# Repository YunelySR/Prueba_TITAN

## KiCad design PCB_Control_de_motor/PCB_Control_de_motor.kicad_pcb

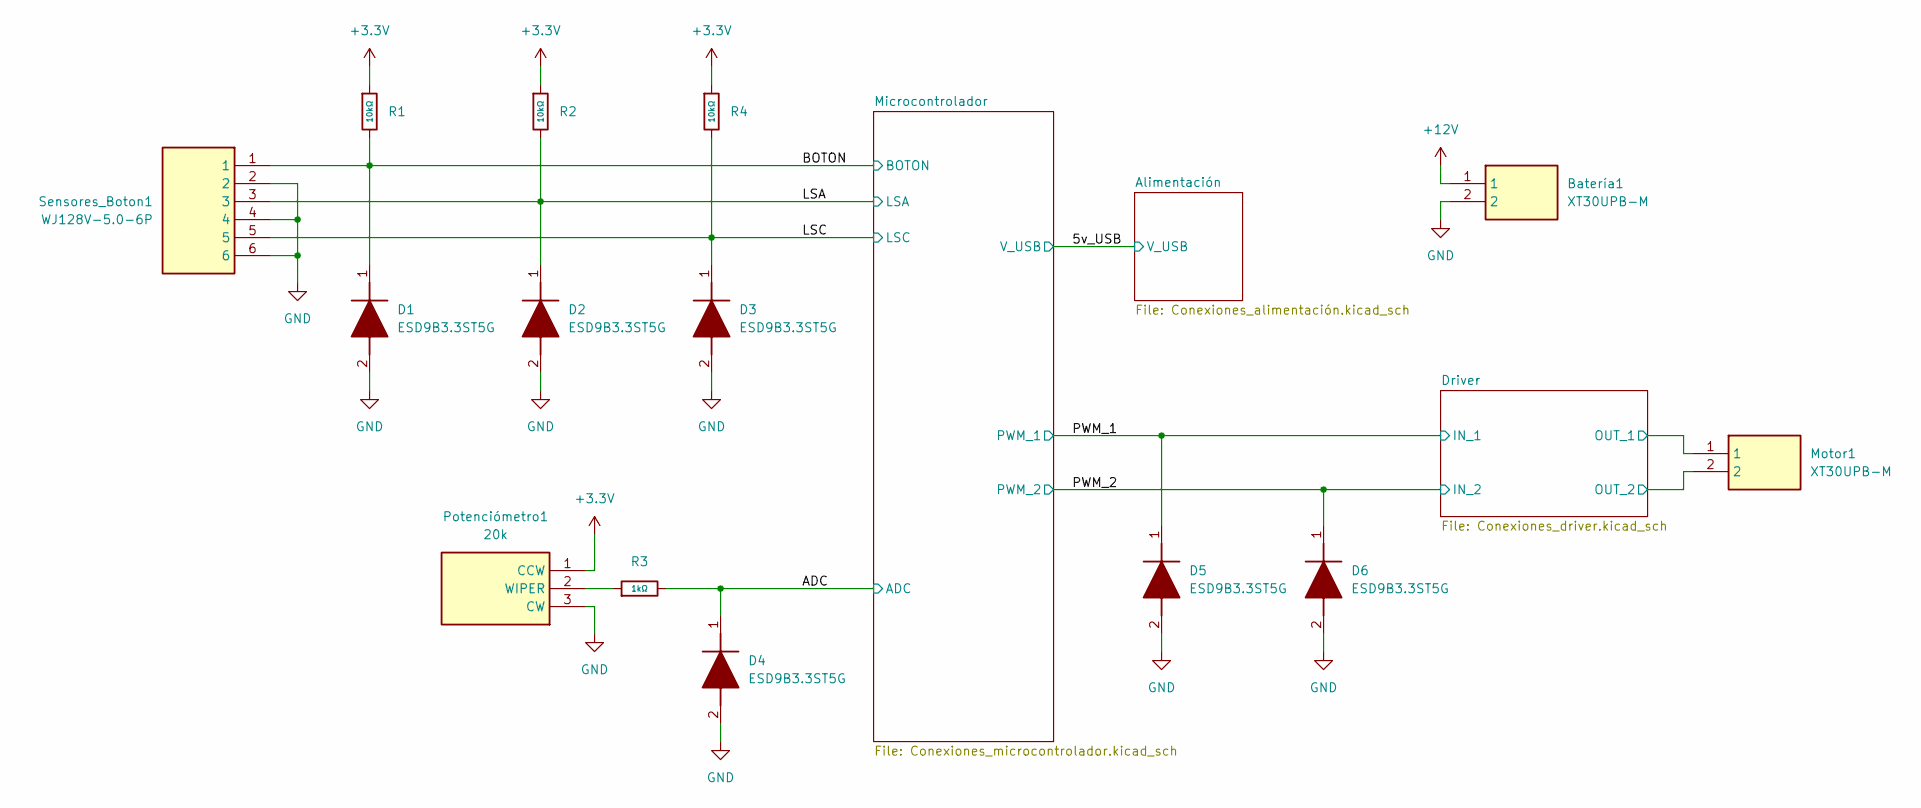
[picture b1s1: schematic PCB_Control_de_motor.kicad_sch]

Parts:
Batería1: XT30UPB-M; SHDR2W160P0X500_1X2_1020X520X1070P; Manufacturer_Part_Number XT30UPB-M
D1, D2, D3, D4, D5, D6: ESD9B3.3ST5G; SODFL1006X40N; Manufacturer_Part_Number ESD9B3.3ST5G; Mouser Part Number 863-ESD9B3.3ST5G
Motor1: XT30UPB-M; SHDR2W160P0X500_1X2_1020X520X1070P; Manufacturer_Part_Number XT30UPB-M
Potenciómetro1: 20k; 3296W1503LF; Manufacturer_Part_Number 3296W-1-203LF; Mouser Part Number 652-3296W-1-203LF
R1, R2, R4: 10kΩ; R_0603; Overload Voltage (Max) 75V; Tolerance ±1%; Part 0603WAF1002T5E; LCSC C25804
R3: 1kΩ; R_0805; Overload Voltage (Max) 150V; Tolerance ±1%; Part 0805W8F1001T5E; LCSC C17513
Sensores_Boton1: WJ128V-5.0-6P; WJ128V506P; Manufacturer_Part_Number WJ128V-5.0-6P

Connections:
+3.3V: Potenciómetro1.1 (CCW), R1.1, R2.1, R4.1; also elsewhere on the board
+12V: Batería1.1; also elsewhere on the board
/ADC: D4.1 (K), R3.2; also elsewhere on the board
/BOTON: D1.1 (K), R1.2, Sensores_Boton1.1; also elsewhere on the board
/Driver/IN_1: D5.1 (K); also elsewhere on the board
/Driver/IN_2: D6.1 (K); also elsewhere on the board
/Driver/OUT_1: Motor1.1; also elsewhere on the board
/Driver/OUT_2: Motor1.2; also elsewhere on the board
/LSA: D2.1 (K), R2.2, Sensores_Boton1.3; also elsewhere on the board
/LSC: D3.1 (K), R4.2, Sensores_Boton1.5; also elsewhere on the board
GND: Batería1.2, D1.2 (A), D2.2 (A), D3.2 (A), D4.2 (A), D5.2 (A), D6.2 (A), Potenciómetro1.3 (CW), Sensores_Boton1.2, Sensores_Boton1.4, Sensores_Boton1.6; also elsewhere on the board
unnamed: Potenciómetro1.2 (WIPER), R3.1

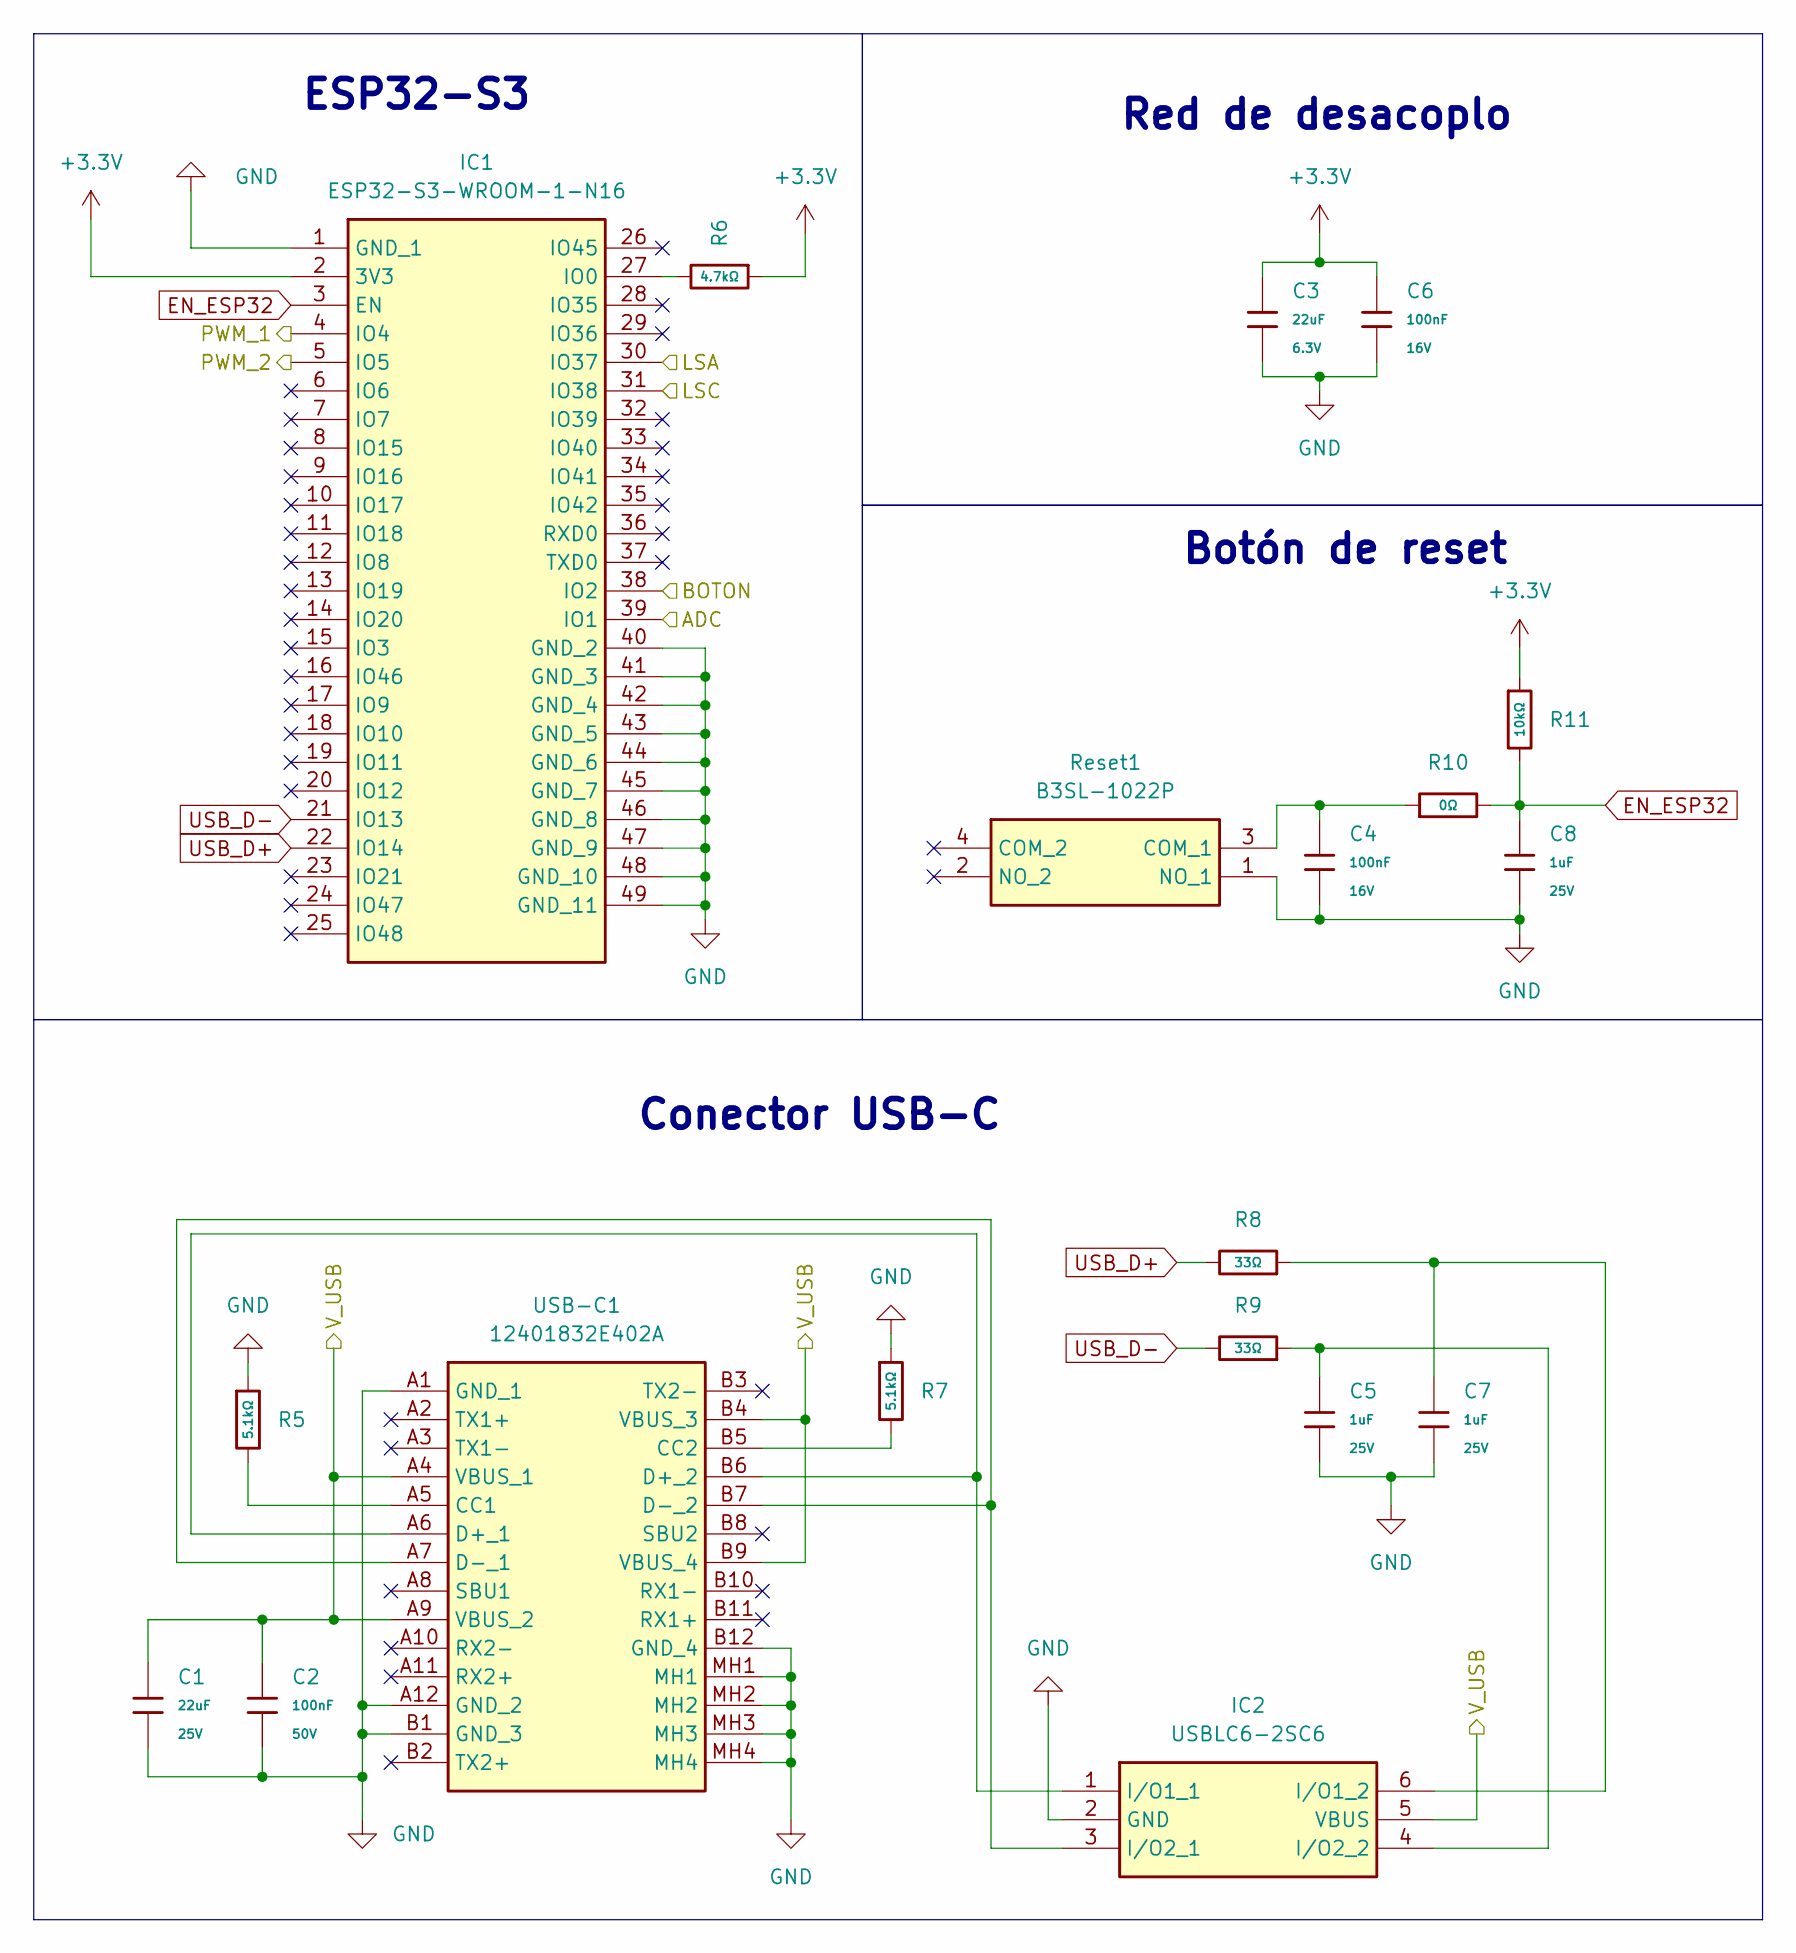
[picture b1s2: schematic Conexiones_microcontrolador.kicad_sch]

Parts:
C1: 22uF; C_0805; Voltage Rated 25V; Tolerance ±20%; Part CL21A226MAQNNNE; LCSC C45783
C2: 100nF; C_0603; Voltage Rated 50V; Tolerance ±10%; Part CC0603KRX7R9BB104; LCSC C14663
C3: 22uF; C_0603; Voltage Rated 6.3V; Tolerance ±20%; Part CL10A226MQ8NRNC; LCSC C59461
C4, C6: 100nF; C_0402; Voltage Rated 16V; Tolerance ±10%; Part CL05B104KO5NNNC; LCSC C1525
C5, C7, C8: 1uF; C_0402; Voltage Rated 25V; Tolerance ±10%; Part CL05A105KA5NQNC; LCSC C52923
IC1: ESP32-S3-WROOM-1-N16; ESP32S3WROOM1N16; Manufacturer_Part_Number ESP32-S3-WROOM-1-N16; Mouser Part Number 356-ESP32S3WROOM1N16
IC2: USBLC6-2SC6; SOT95P280X145-6N; Manufacturer_Part_Number USBLC6-2SC6; Mouser Part Number 511-USBLC6-2SC6
R5, R7: 5.1kΩ; R_0805; Overload Voltage (Max) 150V; Tolerance ±1%; Part 0805W8F5101T5E; LCSC C27834
R6: 4.7kΩ; R_0603; Overload Voltage (Max) 75V; Tolerance ±1%; Part 0603WAF4701T5E; LCSC C23162
R8, R9: 33Ω; R_0603; Overload Voltage (Max) 75V; Tolerance ±1%; Part 0603WAF330JT5E; LCSC C23140
R10: 0Ω; R_0402; Overload Voltage (Max) 50V; Tolerance ±1%; Part 0402WGF0000TCE; LCSC C17168
R11: 10kΩ; R_0805; Overload Voltage (Max) 150V; Tolerance ±1%; Part 0805W8F1002T5E; LCSC C17414
Reset1: B3SL-1022P; B3SL1022P; Manufacturer_Part_Number B3SL-1022P; Mouser Part Number 653-B3SL-1022P
USB-C1: 12401832E402A; Manufacturer_Part_Number 12401832E402A; Mouser Part Number 523-12401832E402A

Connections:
+3.3V: C3.1, C6.1, IC1.2 (3V3), R6.1, R11.1; also elsewhere on the board
/5v_USB: C1.1, C2.1, IC2.5 (VBUS), USB-C1.A4 (VBUS_1), USB-C1.A9 (VBUS_2), USB-C1.B4 (VBUS_3), USB-C1.B9 (VBUS_4); also elsewhere on the board
/ADC: IC1.39 (IO1); also elsewhere on the board
/BOTON: IC1.38 (IO2); also elsewhere on the board
/Driver/IN_1: IC1.4 (IO4); also elsewhere on the board
/Driver/IN_2: IC1.5 (IO5); also elsewhere on the board
/LSA: IC1.30 (IO37); also elsewhere on the board
/LSC: IC1.31 (IO38); also elsewhere on the board
EN_ESP32: C8.1, IC1.3 (EN), R10.2, R11.2
GND: C1.2, C2.2, C3.2, C4.2, C5.2, C6.2, C7.2, C8.2, IC1.1 (GND_1), IC1.40 (GND_2), IC1.41 (GND_3), IC1.42 (GND_4), IC1.43 (GND_5), IC1.44 (GND_6), IC1.45 (GND_7), IC1.46 (GND_8), IC1.47 (GND_9), IC1.48 (GND_10), IC1.49 (GND_11), IC2.2 (GND), R5.1, R7.1, Reset1.1 (NO_1), USB-C1.A1 (GND_1), USB-C1.A12 (GND_2), USB-C1.B1 (GND_3), USB-C1.B12 (GND_4), USB-C1.MH1, USB-C1.MH2, USB-C1.MH3, USB-C1.MH4; also elsewhere on the board
unnamed: IC1.27 (IO0), R6.2
unnamed: IC2.1 (I/O1_1), USB-C1.A6 (D+_1), USB-C1.B6 (D+_2)
unnamed: C7.1, IC2.6 (I/O1_2), R8.1
unnamed: IC2.3 (I/O2_1), USB-C1.A7 (D-_1), USB-C1.B7 (D-_2)
unnamed: C5.1, IC2.4 (I/O2_2), R9.1
unnamed: C4.1, R10.1, Reset1.3 (COM_1)
unnamed: R5.2, USB-C1.A5 (CC1)
unnamed: R7.2, USB-C1.B5 (CC2)
USB_D+: IC1.22 (IO14), R8.2
USB_D-: IC1.21 (IO13), R9.2

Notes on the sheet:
Conector USB-C
ESP32-S3
Botón de reset
Red de desacoplo

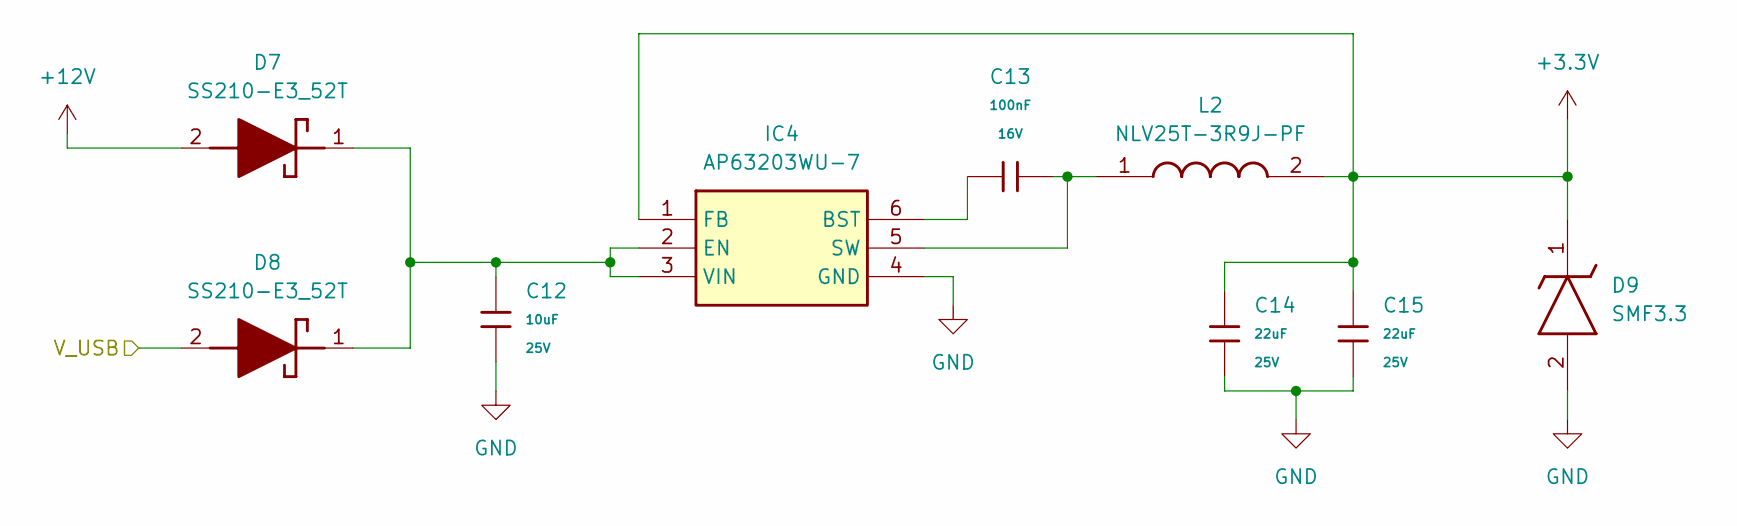
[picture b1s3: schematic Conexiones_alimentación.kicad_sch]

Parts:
C12: 10uF; C_0805; Voltage Rated 25V; Tolerance ±10%; Part CL21A106KAYNNNE; LCSC C15850
C13: 100nF; C_0402; Voltage Rated 16V; Tolerance ±10%; Part CL05B104KO5NNNC; LCSC C1525
C14, C15: 22uF; C_0805; Voltage Rated 25V; Tolerance ±20%; Part CL21A226MAQNNNE; LCSC C45783
D7, D8: SS210-E3_52T; DIONM5436X244N; Manufacturer_Part_Number SS210-E3/52T; Mouser Part Number 625-SS210-E3
D9: SMF3.3; SOD3718X108N; Manufacturer_Part_Number SMF3.3; Mouser Part Number 576-SMF3.3
IC4: AP63203WU-7; AP63203WU7; Manufacturer_Part_Number AP63203WU-7; Mouser Part Number 621-AP63203WU-7
L2: NLV25T-3R9J-PF; INDM2520X190N; Manufacturer_Part_Number NLV25T-3R9J-PF; Mouser Part Number 810-NLV25T-3R9J

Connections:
+3.3V: C14.1, C15.1, D9.1 (K), IC4.1 (FB), L2.2; also elsewhere on the board
+12V: D7.2 (A); also elsewhere on the board
/5v_USB: D8.2 (A); also elsewhere on the board
GND: C12.2, C14.2, C15.2, D9.2 (A), IC4.4 (GND); also elsewhere on the board
unnamed: C12.1, D7.1 (K), D8.1 (K), IC4.2 (EN), IC4.3 (VIN)
unnamed: C13.1, IC4.6 (BST)
unnamed: C13.2, IC4.5 (SW), L2.1

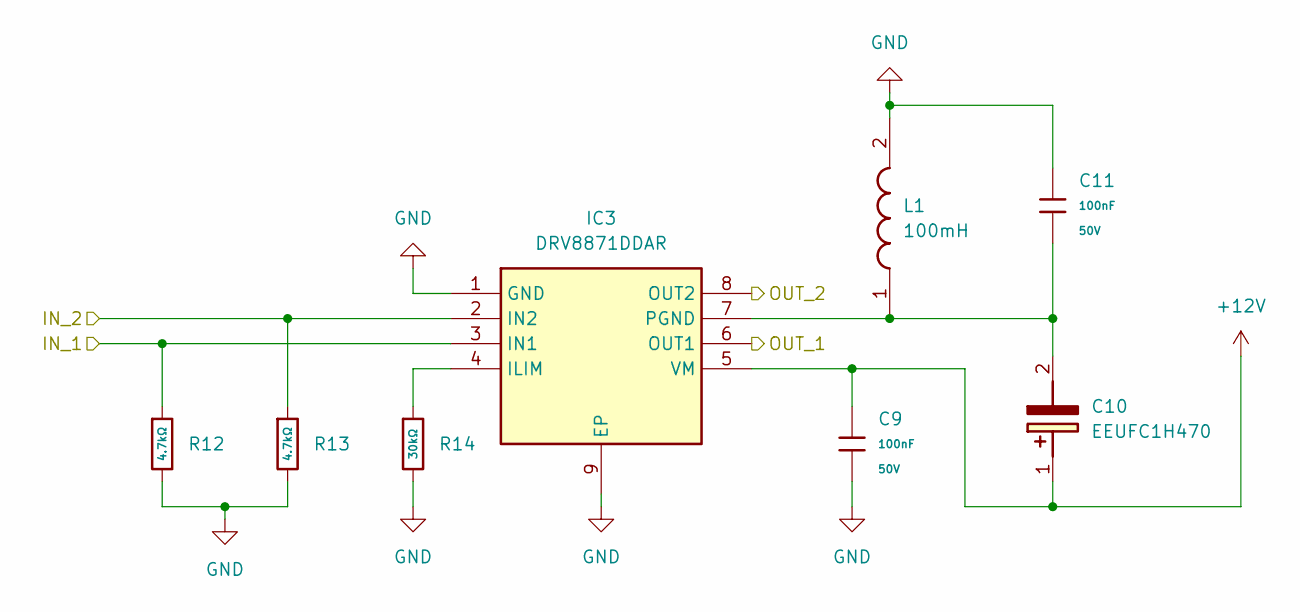
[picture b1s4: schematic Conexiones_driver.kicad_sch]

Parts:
C9, C11: 100nF; C_0603; Voltage Rated 50V; Tolerance ±10%; Part CC0603KRX7R9BB104; LCSC C14663
C10: EEUFC1H470; CAPPRD250W55D630H1220; Manufacturer_Part_Number EEUFC1H470
IC3: DRV8871DDAR; SOIC127P600X170-9N; Manufacturer_Part_Number DRV8871DDAR; Mouser Part Number 595-DRV8871DDAR
L1: 100mH; RLB1014104KL; Manufacturer_Part_Number RLB1014-104KL; Mouser Part Number 652-RLB1014-104KL
R12, R13: 4.7kΩ; R_1206; Overload Voltage (Max) 200V; Tolerance ±1%; Part 1206W4F4701T5E; LCSC C17936
R14: 30kΩ; R_0805; Overload Voltage (Max) 150V; Tolerance ±1%; Part 0805W8F3002T5E; LCSC C17621

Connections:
+12V: C9.1, C10.1 (+), IC3.5 (VM); also elsewhere on the board
/Driver/IN_1: IC3.3 (IN1), R12.1; also elsewhere on the board
/Driver/IN_2: IC3.2 (IN2), R13.1; also elsewhere on the board
/Driver/OUT_1: IC3.6 (OUT1); also elsewhere on the board
/Driver/OUT_2: IC3.8 (OUT2); also elsewhere on the board
GND: C9.2, C11.1, IC3.1 (GND), IC3.9 (EP), L1.2, R12.2, R13.2, R14.2; also elsewhere on the board
unnamed: C10.2 (-), C11.2, IC3.7 (PGND), L1.1
unnamed: IC3.4 (ILIM), R14.1

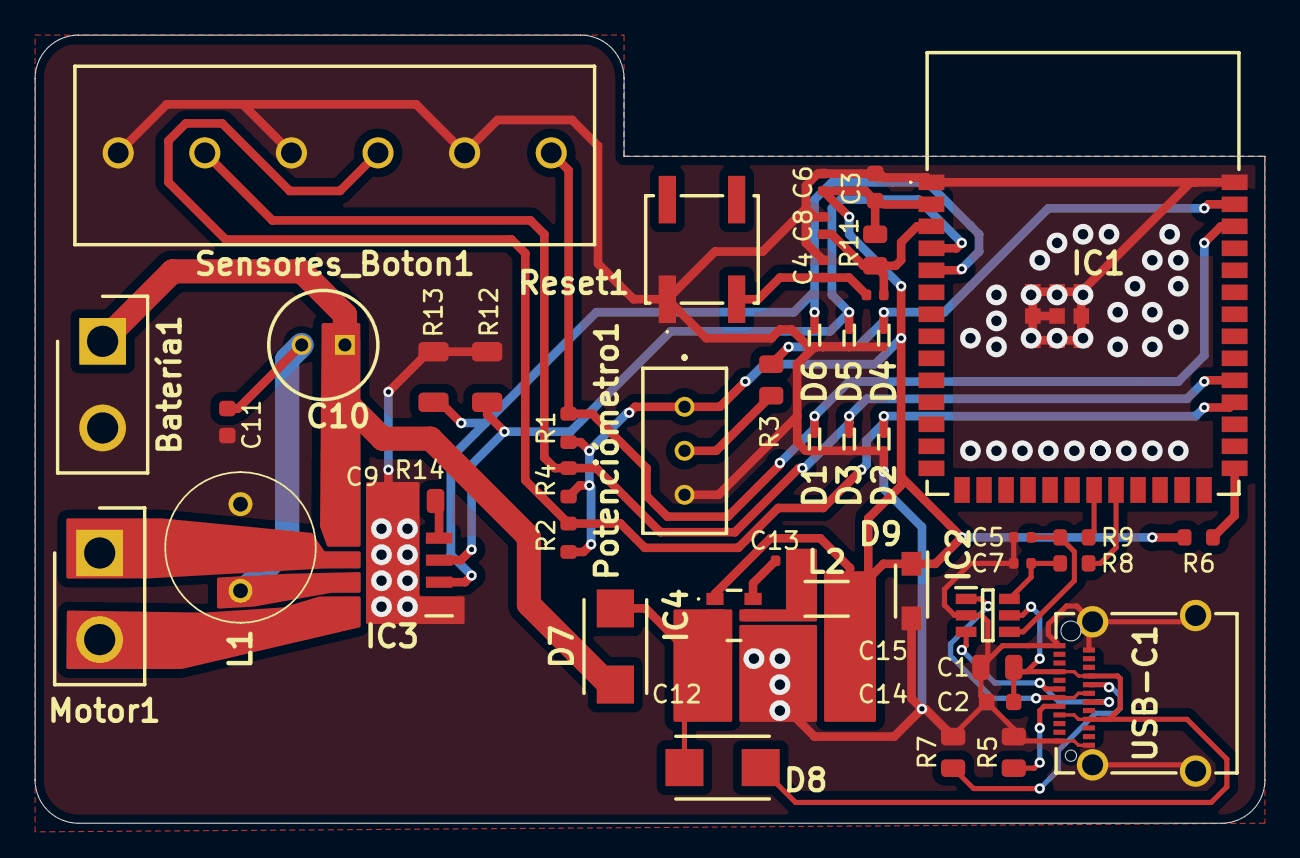
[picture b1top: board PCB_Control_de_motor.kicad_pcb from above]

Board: 2 copper layers, 71.0 x 45.5 mm, 50 parts (0 on the bottom side), 29 nets.

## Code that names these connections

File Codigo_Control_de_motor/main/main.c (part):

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GPIOs de configuración      *       GPIOs del programa
GPIO 0                      *       GPIO 1 - ADC
GPIO 3                      *       GPIO 2 - BOTÓN
GPIO 45                     *       GPIO 37 - LSA
GPIO 46                     *       GPIO 38 - LSC
                            *       GPIO 4 - PWM 1
                            *       GPIO 5 - PWM 2
*/

//Macros para los pines del microcontrolador
#define GPIO_BOTON 2
#define GPIO_LSA 37
#define GPIO_LSC 38
#define GPIO_PWM_1 4
#define GPIO_PWM_2 5

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esp_err_t Configuracion_GPIO(void)
{
    //Reseteamos los pines desacoplándolos de otros periféricos
    gpio_reset_pin(GPIO_BOTON);
    gpio_reset_pin(GPIO_LSA);
    gpio_reset_pin(GPIO_LSC);

    //Definimos si los pines son de entrada o de salida
    gpio_set_direction(GPIO_BOTON, GPIO_MODE_INPUT);
    gpio_set_direction(GPIO_LSA, GPIO_MODE_INPUT);
    gpio_set_direction(GPIO_LSC, GPIO_MODE_INPUT);

    //Inicializamos las variables del debounce en verdadero
    datos_IO.debounce_1 = TRUE;
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void Lectura_GPIO(TimerHandle_t pxTimer)
{
    //Lectura de los GPIOs de los sensores, el botón y el potenciómetro
    datos_IO.LSA = gpio_get_level(GPIO_LSA);
    datos_IO.LSC = gpio_get_level(GPIO_LSC);
    datos_IO.debounce_1 = gpio_get_level(GPIO_BOTON);

    //Aquí hacemos un debounce para el botón
    if (datos_IO.debounce_1 != datos_IO.debounce_2)
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
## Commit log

2025-02-23 Programa listo
2025-02-24 Corrección del código y adelanto del PCB
2025-02-25 Esquemático listo
2025-02-25 Corrección de la huella del ESP32
2025-02-25 Corrección 2 del esquemático
2025-02-25 Corrección 3 del esquemático
2025-02-26 Agregado de diodos TVS y avance del PCB con fuente y micro listo
2025-02-26 PCB casi terminado
2025-02-26 PCB listo
2025-02-26 Correción del PCB, archivos de fabricación y BOM
2025-02-28 Cambio del capacitor y rediseño de las pistas del driver con sus componentes
2025-03-03 Eliminación de las vías en la bobina del power ground
